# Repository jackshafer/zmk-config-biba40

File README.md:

# Biba40
## The BIBA40 is a compact, split, wireless keyboard powered by ZMK firmware and two microcontrollers.

A 40% Split Ortholiner wireless keyboard powered by ZMK.

* Keyboard Maintainer: [Daniel Biba](https://github.com/danbiba)
* Hardware Supported: nice!nano v2, Supermini NRF52840
* Hardware Availability: 3D Printable
* Buy your own : https://bibakeyboards.com/

## Keymap
### Default Layer

### Lower Layer

### Raise Layer

### Adjust Layer

### Function Layer

## Setup
Clone the repository located at https://github.com/danbiba/zmk-config-biba40

Compile the firmware using Github actions. This will produce 3 files:

* biba40_left-nice_nano_v2-zmk.uf2
* biba40_right-nice_nano_v2-zmk.uf2
* settings_reset-nice_nano_v2-zmk.uf2

## Bootloader

Enter the bootloader in 3 ways:

* Lower + 0,3 (for the left board)
* Raise + 5,3 (for the right board)
* Short out pins RST and GND on the nice!nano v2

[View the BIBA40 V2 Build Guide](Build_Guide.md)

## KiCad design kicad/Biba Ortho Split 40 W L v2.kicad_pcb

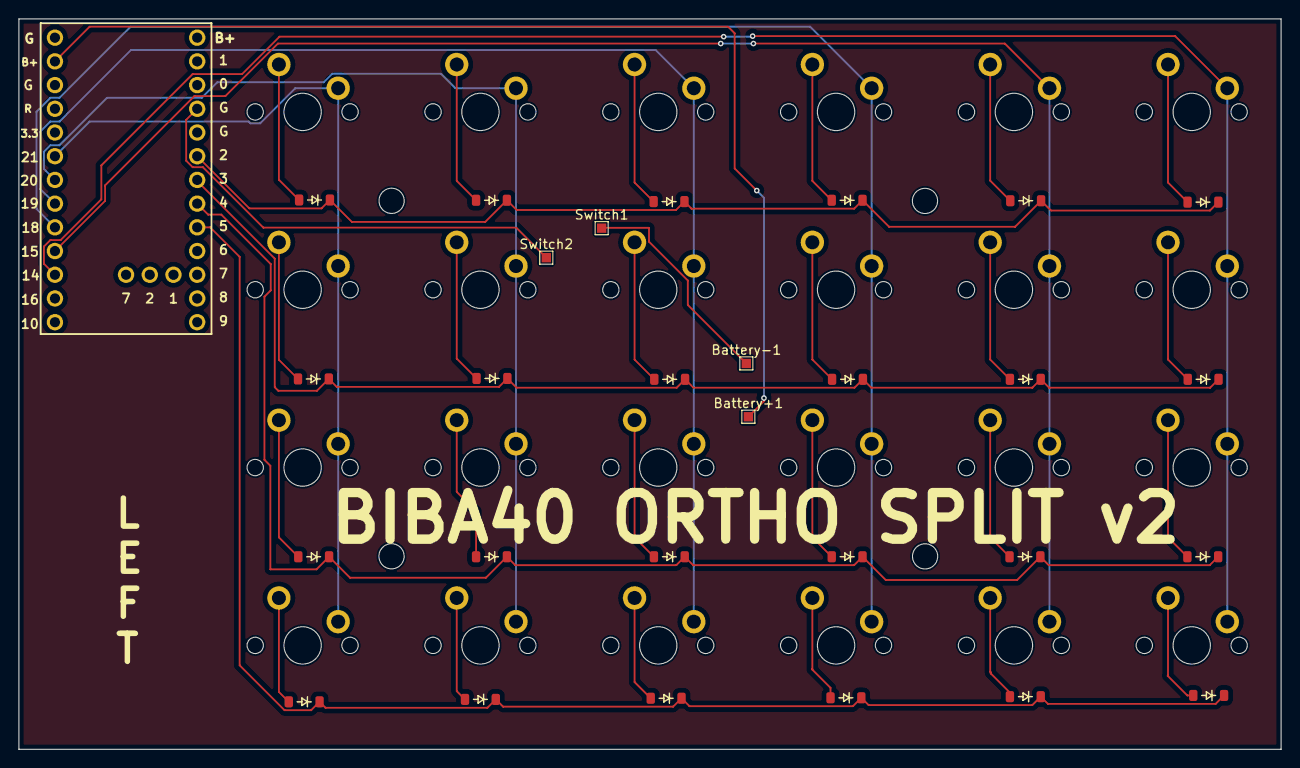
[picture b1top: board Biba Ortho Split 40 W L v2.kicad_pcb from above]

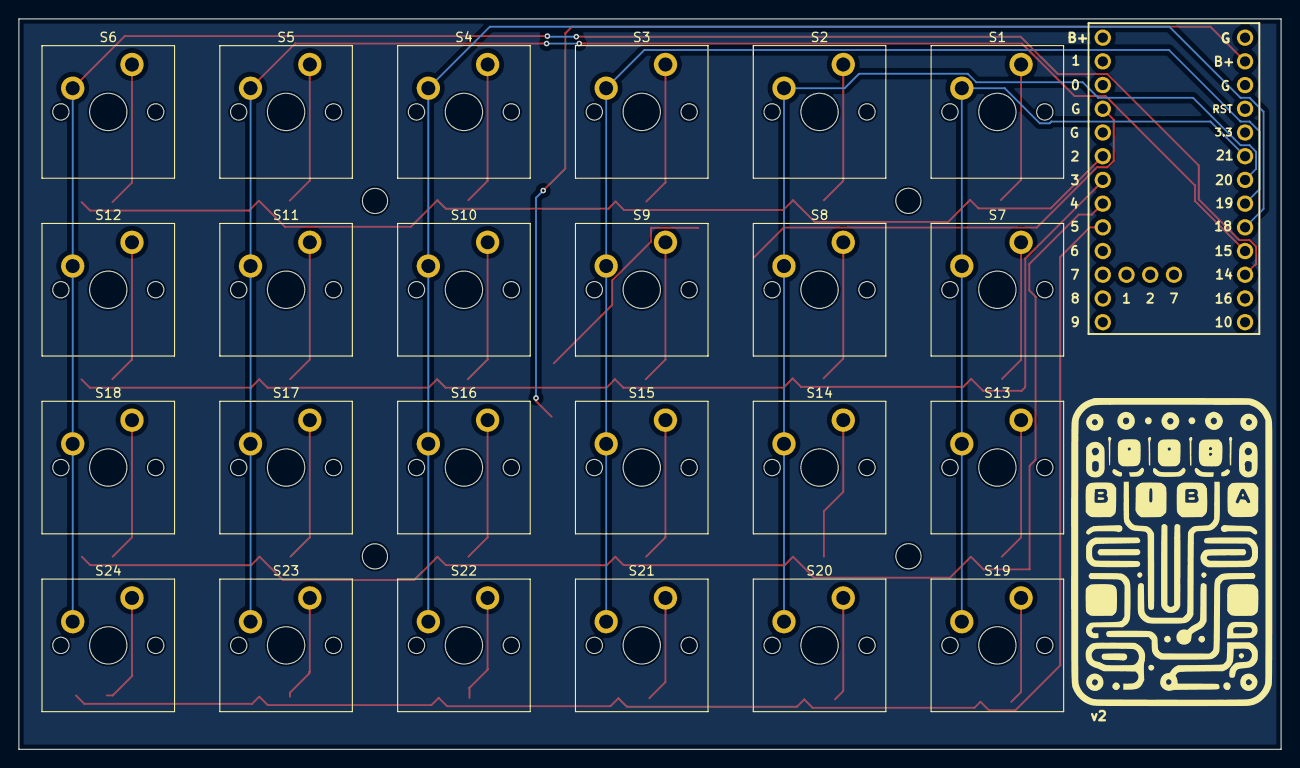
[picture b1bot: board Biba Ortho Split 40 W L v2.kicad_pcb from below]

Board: 2 copper layers, 135.2 x 78.2 mm, 53 parts (25 on the bottom side), 37 nets.

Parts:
Battery+1: Battery +; TestPoint_Pad_1.0x1.0mm
Battery-1: Battery -; TestPoint_Pad_1.0x1.0mm
D1, D2, D3, D4, D5, D6, D7, D8, D9, D10, D11, D12, D13, D14, D15, D16, D17, D18, D19, D20, D21, D22, D23, D24: Diode; Diode_SOD-123
S1, S2, S3, S4, S5, S6, S7, S8, S9, S10, S11, S12, S13, S14, S15, S16, S17, S18, S19, S20, S21, S22, S23, S24: Keyswitch; MX_PCB_1.00u
Switch1: Switch 1; TestPoint_Pad_1.0x1.0mm
Switch2: Switch 2; TestPoint_Pad_1.0x1.0mm
U1: SuperMini NRF52840

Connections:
Battery +: Battery+1.1, U1.24 (B+)
Battery -: Battery-1.1, Switch1.1
Column 0: S1.1, S7.1, S13.1, S19.1, U1.20 (21)
Column 1: S2.1, S8.1, S14.1, S20.1, U1.19 (20)
Column 2: S3.1, S9.1, S15.1, S21.1, U1.18 (19)
Column 3: S4.1, S10.1, S16.1, S22.1, U1.17 (18)
Column 4: S5.1, S11.1, S17.1, S23.1, U1.16 (15)
Column 5: S6.1, S12.1, S18.1, S24.1, U1.15 (14)
unnamed: D1.2 (A), S1.2
unnamed: D2.2 (A), S2.2
unnamed: D3.2 (A), S3.2
unnamed: D4.2 (A), S4.2
unnamed: D5.2 (A), S5.2
unnamed: D6.2 (A), S6.2
unnamed: D7.2 (A), S7.2
unnamed: D8.2 (A), S8.2
unnamed: D9.2 (A), S9.2
unnamed: D10.2 (A), S10.2
unnamed: D11.2 (A), S11.2
unnamed: D12.2 (A), S12.2
unnamed: D13.2 (A), S13.2
unnamed: D14.2 (A), S14.2
unnamed: D15.2 (A), S15.2
unnamed: D16.2 (A), S16.2
unnamed: D17.2 (A), S17.2
unnamed: D18.2 (A), S18.2
unnamed: D19.2 (A), S19.2
unnamed: D20.2 (A), S20.2
unnamed: D21.2 (A), S21.2
unnamed: D22.2 (A), S22.2
unnamed: D23.2 (A), S23.2
unnamed: D24.2 (A), S24.2
Row 0: D1.1 (K), D2.1 (K), D3.1 (K), D4.1 (K), D5.1 (K), D6.1 (K), U1.5 (2)
Row 1: D7.1 (K), D8.1 (K), D9.1 (K), D10.1 (K), D11.1 (K), D12.1 (K), U1.6 (3)
Row 2: D13.1 (K), D14.1 (K), D15.1 (K), D16.1 (K), D17.1 (K), D18.1 (K), U1.7 (4)
Row 3: D19.1 (K), D20.1 (K), D21.1 (K), D22.1 (K), D23.1 (K), D24.1 (K), U1.8 (5)
Switch1: Switch2.1, U1.3 (GND)

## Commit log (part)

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2024-10-09 Initial User Config.
2024-10-09 Compile
2024-10-12 Create README.md
    Created README.md doc
2024-10-14 Update biba40.keymap and Compile
2024-10-29 Update biba40.keymap
    Swapped LALT and LGUI on the left half.
2024-11-13 Update build.yaml
    Added ZMK studio snippet
2024-11-13 Update biba40.conf
    Added config ZMK studio
2024-11-13 Update biba40.keymap
    Added ZMK Studio Unlock to keymap
2025-05-19 Update biba40.keymap
    added equal symbol that was missing from RAISE layer
2025-05-19 Update biba40.keymap
    equal fix
2025-05-19 equal symbol
2025-05-19 equal symbol take 2
2025-05-19 Rename build.yaml to zmk.yaml
2025-05-19 Rename zmk.yaml to zmk.yml
2025-05-19 Rename zmk.yml to build.yaml
2025-05-19 Force rebuild
2025-08-11 Update west.yml
    Pin ZMK version to v0.2
2025-09-30 Create info.json
    enable Keymap editor
2025-09-30 Create prj.conf
    Added Mouse support
2025-10-01 Update prj.conf
    mouse changed to pointing
2025-10-01 Update biba40.keymap
    added pointing
2025-10-01 Update biba40.keymap
    mouse test
2025-10-01 Fix Esc key
2025-10-01 take 2
2025-10-06 Update biba40.conf
    Mouse adjustment
2025-10-08 Create Build_Guide.md
    Creation of Build Guide
2025-10-08 Rename Biba40 Case v2 v19.png to Biba40_Case_v2.png
2025-10-08 Rename Biba40 Battery Cover v2 v19.png to Biba40_Battery_Cover_v2.png
2025-10-08 Rename Biba40 Alignment Plate v2.png to Biba40_Alignment_Plate_v2.png
2025-10-08 Rename Biba40 Case rev 3.3mf to Biba40 Case Kit Sliced.3mf
2025-10-08 Rename PXL_20251002_191923528.PORTRAIT.ORIGINAL.jpg to Glamour_Shot.jpg
2025-10-08 Rename kicad/Production/Biba_Ortho_Split_40_W_L.zip to kicad/Production/OLD/Biba_Ortho_Split_40_W_L.zip
2025-10-08 Rename kicad/Production/Biba_Ortho_Split_40_W_R.zip to kicad/Production/OLD/Biba_Ortho_Split_40_W_R.zip
2025-10-10 Delete boards/shields/biba40/biba40.keymap
    File cleanup
2025-10-10 Update biba40.keymap
    Added mouse movements to FUNCTION layer
2025-10-10 Update biba40.keymap
    Added mouse clicks (left and right) to function layer
2025-10-10 Update biba40.keymap
    build(studio): enable Studio on left via snippet and CONFIG_ZMK_STUDIO
    ci: use ZMK build-user-config workflow @main
    west: track ZMK main for Studio testing
    keymap: add &studio_unlock on FUNCTION
2025-10-10 Update biba40.dtsi
    Changed from Matrix transform to Physical Layout
2025-10-14 fIrst updated repo 10-13-25
2025-10-14 AutoshIft added
2025-10-14 Complete &as keymap
2025-10-14 Updated biba40.keymap
2026-04-01 April 1 2026
2026-04-01 revert west.yml
2026-04-01 Change board name from nice_nano_v2 to nice_nano
2026-04-01 Update board references to include '//zmk' suffix
2026-04-01 second 4 1 26
2026-04-09 April 9
2026-05-04 may 4
2026-05-06 May 6
2026-05-09 may 9
2026-06-12 June 12 2026
2026-06-18 June 17 2026
2026-06-21 Add Bluetooth stability enhancements to config
    Added Bluetooth stability enhancements configuration.
2026-06-23 Add Bluetooth stability and clock control configurations
2026-06-26 June 26 2026
